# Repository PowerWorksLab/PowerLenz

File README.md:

# PowerLenz

PowerLenz - Power monitoring, management and analytics platform.

PowerLenz is a Sense-style energy monitor for Indian single-phase homes (230 V, 50 Hz). A clamp-on current sensor and a voltage sensor feed a 24-bit simultaneous-sampling ADC and an ESP32-S3, which finds appliance switching events and sends them to the cloud for classification. The hardware design is at paper stage: it is datasheet-checked, but nothing has been built or bench-tested yet.

## Documentation

Start with **[documentation/README.md](documentation/README.md)**. It gives the reading order, the design and its decisions, the bill of materials summary, safety notes and what is still open.

| Where | What it holds |
|---|---|
| [documentation/README.md](documentation/README.md) | The whole design in one page, with the reading order |
| [documentation/findings/](documentation/findings/) | Design reasoning, the datasheet verification checklist, datasheet links and the [bill of materials](documentation/findings/bill-of-materials.md) |
| [documentation/datasheets/](documentation/datasheets/README.md) | Local copies of the manufacturer datasheets, organised by function |
| [documentation/diagrams/](documentation/diagrams/) | Circuit diagrams and the calculation page |
| [documentation/presentations/](documentation/presentations/) | The slide deck and the scripts that build it |
| [documentation/brand/](documentation/brand/brand-guidelines.md) | Brand guidelines, [company purpose](documentation/brand/company-purpose.md), brand kit and sample screens |

## Safety

The mains side of the design is live 230 V. Nothing here is ready to be powered from the mains. Use an enclosure, correct clearance and creepage, and have the board reviewed by someone with mains-design experience first.

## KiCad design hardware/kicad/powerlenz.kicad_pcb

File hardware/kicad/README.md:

# KiCad design

The PowerLenz schematic, written as code and checked with KiCad's own electrical rules check (ERC).

| File | What it is |
|---|---|
| `powerlenz.kicad_pro` | KiCad project |
| `powerlenz.kicad_sch` | The schematic. **Generated**: edit `tools/build_schematic.py`, then re-run it. Hand edits in KiCad are overwritten. |
| `tools/build_schematic.py` | Describes the circuit, one function per block |
| `tools/kicad_gen.py`, `sexp.py`, `libinfo.py` | A small generator that takes symbols from KiCad's installed libraries |
| `sym-lib-table`, `fp-lib-table` | Library paths for the project |

## Rebuild and check

```
cd hardware/kicad
python3 tools/build_schematic.py
kicad-cli sch erc --format json --severity-all -o erc.json powerlenz.kicad_sch
kicad-cli sch export netlist --format kicadsexpr -o powerlenz.net powerlenz.kicad_sch
kicad-cli sch export pdf -o powerlenz.pdf powerlenz.kicad_sch
```

Needs KiCad 10 (`kicad-cli`) and Python 3. Connections are made with net labels and power symbols: every pin carrying the same net name is connected.

## PCB and 3D model

`tools/build_pcb.py` builds `powerlenz.kicad_pcb` from the schematic netlist: all parts are placed on a compact 154 x 86 mm board (with the ESP32-S3 DevKitC plugged into two 1x22 sockets; its outline and 22.86 mm row spacing are assumed) with a mains zone and a low-voltage zone, and every pad is assigned its net. `tools/route.py` then routes it with Freerouting in two separate runs (needs Java and the Freerouting jar in `~/tools`, not stored in the repo): the low-voltage side (0.25 mm signals, 0.5 mm power, 0.2 mm clearance, GND pour on the back copper) and the mains nets `L_IN`, `L_FUSED`, `N`, `ZA_P`, `ZP1`, `ZP2` (0.8 mm tracks, 3 mm clearance, the `Mains` net class in `powerlenz.kicad_pro`). Two 1 mm slots are milled along the isolation line at x = 56 mm (Edge.Cuts); `powerlenz.kicad_dru` relaxes the rule only for the terminal block J1, whose own pad gap is 2.48 mm.

**DRAFT: the mains clearance, the slot and the isolation spacing are my starting values (roughly IEC 60664-1 basic creepage for 250 V, pollution degree 2, plus margin) and have not been reviewed by anyone with mains-design experience.** Do not build this board. DRC reports no clearance, short or unconnected errors, only silkscreen and library-copy warnings.

```
python3 tools/build_pcb.py        # after the schematic is built
python3 tools/route.py            # needs ~/tools/freerouting*.jar; removes old tracks, then routes
kicad-cli pcb render --side top --rotate '-45,0,25' --width 2400 --height 1600 --quality high -o exports/3d/powerlenz-pcb-3d.png powerlenz.kicad_pcb
kicad-cli pcb export glb --subst-models -o exports/3d/powerlenz-pcb.glb powerlenz.kicad_pcb
python3 tools/make_step_models.py   # STEP stand-ins for the ZMPT107-1, DevKitC and fuse clip
kicad-cli pcb export step --subst-models --include-tracks --include-pads --include-zones --include-silkscreen --include-soldermask -o exports/3d/powerlenz-pcb.step powerlenz.kicad_pcb
```

| File | What it is |
|---|---|
| `exports/3d/powerlenz-pcb-3d.png`, `powerlenz-pcb-top.png` | Rendered pictures of the board |
| `exports/3d/powerlenz-pcb.glb` | The full 3D model (open in Blender, or any glTF viewer) |
| `exports/3d/powerlenz-pcb.step` | STEP for SolidWorks and other mechanical CAD, with copper, pads, silkscreen, solder mask and every part. The ZMPT107-1, the DevKitC and the fuse clip are simple coloured boxes from `tools/make_step_models.py` (assumed sizes, not manufacturer geometry); the other parts are KiCad library models. In SolidWorks use Open, Options, Import as assembly. |

Things to know about the 3D model:
- The ZMPT107-1 is a simple box (19 x 10 x 18.2 mm) with four pins, from the manufacturer's drawing, with its footprint taken from the same drawing and not yet checked against a real part.
- The varistor uses a 12 mm disc footprint as the nearest match for the 10 mm 10D561K.
- The BAT54 and BAV199 SOT-23 pad mappings are assumed (see the part notes).
- The mains and low-voltage zones are marked on the board. A real board also needs an isolation slot and proper creepage and clearance, reviewed by someone with mains-design experience.

## ERC notes

- `same_local_global_label` is set to ignore in `powerlenz.kicad_pro`. A few pins use a plain net label with the same name as a power net (for example +3V3A or GND) to keep stacked power symbols from overlapping. The nets are the same either way, and the exported netlist was compared before and after to confirm that.
- Footprints are not assigned yet, so the board stage is still ahead.

## Exports

`exports/powerlenz-schematic.pdf` and `exports/powerlenz-bom.csv` are generated with `kicad-cli` (see above). Re-export after any change.

## Status

The schematic is built block by block. Each block is committed once its ERC is clean. Footprints are not assigned yet. Nothing here has been built or tested; the open items in `documentation/README.md` still apply, and the mains side needs a design review before it is ever powered.

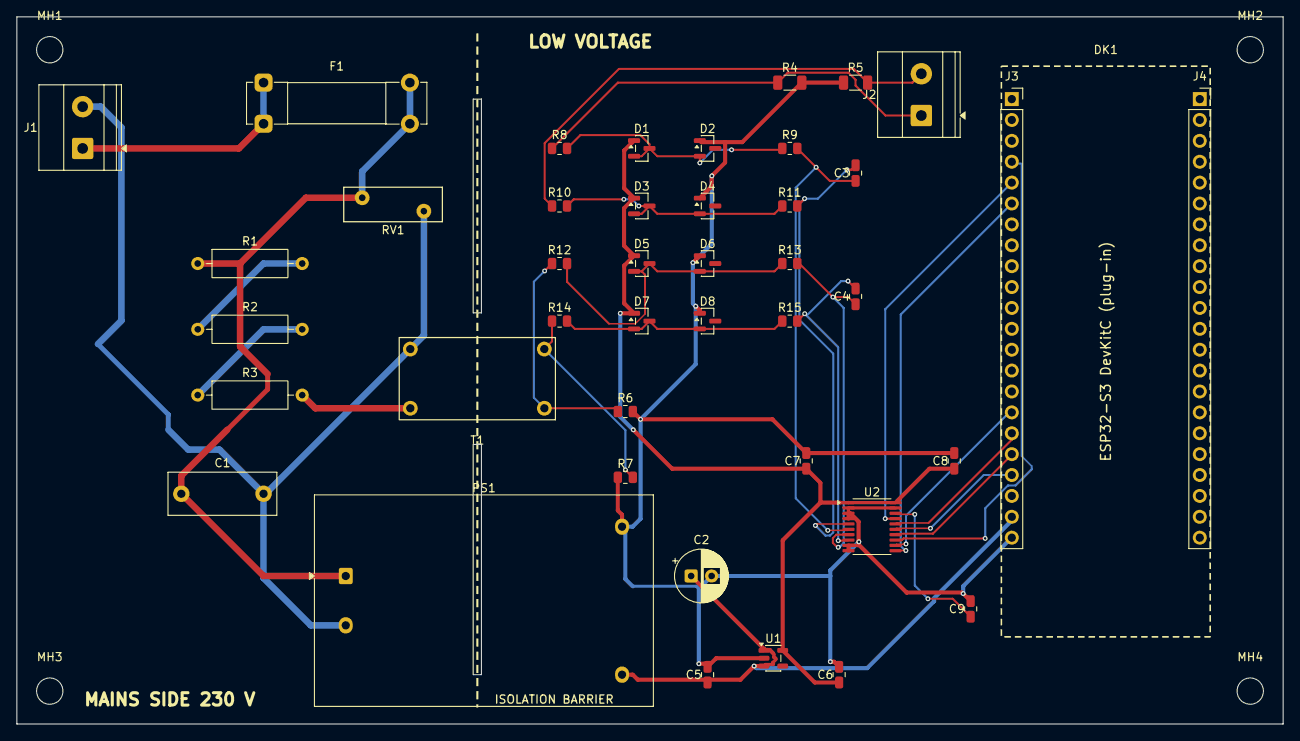
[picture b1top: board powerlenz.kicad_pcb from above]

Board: 2 copper layers, 154.0 x 86.0 mm, 47 parts (0 on the bottom side), 29 nets.

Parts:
C1: 0.1uF X2 275VAC; C_Rect_L13.0mm_W5.0mm_P10.00mm_FKS3_FKP3_MKS4
C2: 220uF 25V; CP_Radial_D6.3mm_P2.50mm
C3, C4: 10nF C0G; C_0805_2012Metric
C5, C6, C7, C8: 1uF 50V X7R; C_0805_2012Metric
C9: 220nF 50V X7R; C_0805_2012Metric
D1, D3, D5, D7: BAT54; SOT-23
D2, D4, D6, D8: BAV199; SOT-23
DK1: ESP32-S3-DevKitC-1
F1: 1A T 250V; Fuseholder_Clip-5x20mm_Bel_FC-203-22_Lateral_P17.80x5.00mm_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
J1: Mains in; TerminalBlock_Phoenix_MKDS-1,5-2-5.08_1x02_P5.08mm_Horizont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
J2: CT SCT-013-000; TerminalBlock_Phoenix_MKDS-1,5-2-5.08_1x02_P5.08mm_Horizont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
J3: DevKitC row A (J1 pins); PinSocket_1x22_P2.54mm_Vertical
J4: DevKitC row B (J3 pins); PinSocket_1x22_P2.54mm_Vertical
MH1, MH2, MH3, MH4: MountingHole_3.2mm_M3
PS1: HLK-5M05; Converter_ACDC_Hi-Link_HLK-5Mxx
R1, R2, R3: 39k 1% 1/2W; R_Axial_DIN0309_L9.0mm_D3.2mm_P12.70mm_Horizontal
R4, R5: 6.49R 1%; R_1206_3216Metric
R6, R7: 24.9R 1%; R_0805_2012Metric
R8, R10, R12, R14: 1k 1%; R_0805_2012Metric
R9, R11, R13, R15: 100R 1%; R_0805_2012Metric
RV1: 10D561K; RV_Disc_D12mm_W4.2mm_P7.5mm
T1: ZMPT107-1
U1: LP5907-3.3; SOT-23-5
U2: ADS131M04; TSSOP-20_4.4x6.5mm_P0.65mm

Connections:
+3V3A: C6.1, C7.1, C8.1, D1.1, D3.1, D5.1, D7.1, U1.5, U2.1, U2.20
+5V: C2.1, C5.1, J3.21, PS1.4, U1.1, U1.3
ADC_CAP: C9.1, U2.18
ADC_CLKIN: J3.5, U2.17
ADC_CS: J3.16, U2.12
ADC_DIN: J3.17, U2.16
ADC_DOUT: J3.19, U2.15
ADC_DRDY: J3.4, U2.13
ADC_RESET: J3.6, U2.11
ADC_SCLK: J3.18, U2.14
CH1N: C3.2, R11.2, U2.5
CH1P: C3.1, R9.2, U2.6
CH2N: C4.2, R15.2, U2.8
CH2P: C4.1, R13.2, U2.7
CT_N: J2.2, R5.2, R10.1
CT_N_C: D3.2, D3.3, D4.2, R10.2, R11.1
CT_P: J2.1, R4.1, R8.1
CT_P_C: D1.2, D1.3, D2.2, R8.2, R9.1
GND: C2.2, C5.2, C6.2, C7.2, C8.2, C9.2, D2.1, D4.1, D6.1, D8.1, J3.22, PS1.3, R4.2, R5.1, R6.2, R7.1, U1.2, U2.2, U2.3, U2.4, U2.9, U2.10, U2.19
L_FUSED: C1.1, F1.2, PS1.1, R1.1, RV1.1
L_IN: F1.1, J1.1
N: C1.2, J1.2, PS1.2, RV1.2, T1.1
V_N: R7.2, R14.1, T1.3
V_N_C: D7.2, D7.3, D8.2, R14.2, R15.1
V_P: R6.1, R12.1, T1.4
V_P_C: D5.2, D5.3, D6.2, R12.2, R13.1
ZA_P: R3.2, T1.2
ZP1: R1.2, R2.1
ZP2: R2.2, R3.1

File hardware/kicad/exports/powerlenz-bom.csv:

"Reference","Value","Qty","Footprint","MPN","Manufacturer"
"C1","0.1uF X2 275VAC","1","Capacitor_THT:C_Rect_L13.0mm_W5.0mm_P10.00mm_FKS3_FKP3_MKS4","",""
"C2","220uF 25V","1","Capacitor_THT:CP_Radial_D6.3mm_P2.50mm","",""
"C3,C4","10nF C0G","2","Capacitor_SMD:C_0805_2012Metric","0805N103J500CT","Walsin"
"C5,C6,C7,C8","1uF 50V X7R","4","Capacitor_SMD:C_0805_2012Metric","CC0805KKX7R9BB105","Yageo"
"C9","220nF 50V X7R","1","Capacitor_SMD:C_0805_2012Metric","0805B224K500CT","Walsin"
"D1,D3,D5,D7","BAT54","4","Package_TO_SOT_SMD:SOT-23","BAT54-7-F","Diodes Inc"
"D2,D4,D6,D8","BAV199","4","Package_TO_SOT_SMD:SOT-23","BAV199-7-F","Diodes Inc"
"F1","1A T 250V","1","Fuse:Fuseholder_Clip-5x20mm_Bel_FC-203-22_Lateral_P17.80x5.00mm_D1.17mm_Horizontal","5HT 1-R","Bel Fuse"
"J1","Mains in","1","TerminalBlock_Phoenix:TerminalBlock_Phoenix_MKDS-1,5-2-5.08_1x02_P5.08mm_Horizontal","",""
"J2","CT SCT-013-000","1","TerminalBlock_Phoenix:TerminalBlock_Phoenix_MKDS-1,5-2-5.08_1x02_P5.08mm_Horizontal","",""
"J3","To DevKitC","1","Connector_PinHeader_2.54mm:PinHeader_1x09_P2.54mm_Vertical","",""
"PS1","HLK-5M05","1","Converter_ACDC:Converter_ACDC_Hi-Link_HLK-5Mxx","","Hi-Link"
"R1,R2,R3","39k 1% 1/2W","3","Resistor_THT:R_Axial_DIN0309_L9.0mm_D3.2mm_P12.70mm_Horizontal","MF50 39K",""
"R4,R5","6.49R 1%","2","Resistor_SMD:R_1206_3216Metric","CRCW12066R49FKEA","Vishay"
"R6,R7","24.9R 1%","2","Resistor_SMD:R_0805_2012Metric","RC0805FR-0724R9L","Yageo"
"R8,R10,R12,R14","1k 1%","4","Resistor_SMD:R_0805_2012Metric","RC0805FR-071KL","Yageo"
"R9,R11,R13,R15","100R 1%","4","Resistor_SMD:R_0805_2012Metric","RC0805FR-07100RL","Yageo"
"RV1","10D561K","1","Varistor:RV_Disc_D12mm_W4.2mm_P7.5mm","MOV-10D561K","Bourns"
"T1","ZMPT107-1","1","powerlenz:ZMPT107-1","","Zeming"
"U1","LP5907-3.3","1","Package_TO_SOT_SMD:SOT-23-5","LP5907MFX-3.3/NOPB","Texas Instruments"
"U2","ADS131M04","1","Package_SO:TSSOP-20_4.4x6.5mm_P0.65mm","ADS131M04IPWR","Texas Instruments"

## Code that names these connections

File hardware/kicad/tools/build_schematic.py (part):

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    y = 60.96
    s.part("Connector", "Screw_Terminal_01x02", "Mains in", (33.02, y), {1: "L_IN", 2: "N"}, prefix="J",
           extra={"Note": "Pin 1 = live, pin 2 = neutral"})
    s.part("Device", "Fuse", "1A T 250V", (68.58, y), {1: "L_IN", 2: "L_FUSED"}, prefix="F", rot=90,
           extra={"MPN": "5HT 1-R", "Manufacturer": "Bel Fuse",
                  "Note": "Ceramic time-lag, listed 1.5 kA at 250 VAC; Bel datasheet not yet read"})
    s.part("Device", "Varistor", "10D561K", (101.6, y), {1: "L_FUSED", 2: "N"}, prefix="RV", rot=90,
           extra={"MPN": "MOV-10D561K", "Manufacturer": "Bourns", "Note": "350 VAC / 460 VDC, 2.5 kA, 70 J"})
    # ZMPT107-1 primary string: 3 x 39 k in series = 117 k (about 2 mA at 230 V)
    s.part("Device", "R", "39k 1% 1/2W", (132.08, y), {1: "L_FUSED", 2: "ZP1"}, prefix="R", rot=90,
           extra={"MPN": "MF50 39K", "Note": "Series string R1-R3 sets about 2 mA through the ZMPT107-1 primary"})
    s.part("Device", "R", "39k 1% 1/2W", (157.48, y), {1: "ZP1", 2: "ZP2"}, prefix="R", rot=90,
           extra={"MPN": "MF50 39K"})
    s.part("Device", "R", "39k 1% 1/2W", (182.88, y), {1: "ZP2", 2: "ZA_P"}, prefix="R", rot=90,
           extra={"MPN": "MF50 39K"})
    s.part("Device", "Transformer_1P_1S", "ZMPT107-1", (228.6, y), {1: "ZA_P", 2: "N", 4: "V_P", 3: "V_N"}, prefix="T",
           extra={"Manufacturer": "Zeming", "Note": "2 mA : 2 mA, 3000 V isolated. Windings are interchangeable (1000:1000); "
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    s.text("CT current sensor: burden 2 x 6.49 ohm, midpoint to GND", 15.24, 152.4, 1.27)
    s.part("Connector", "Screw_Terminal_01x02", "CT SCT-013-000", (25.4, yi), {1: "CT_P", 2: "CT_N"}, prefix="J",
           extra={"Note": "Current-output CT (100 A : 50 mA). Never leave the CT secondary open"})
    s.part("Device", "R", "6.49R 1%", (68.58, yi), {1: "CT_P", 2: "GND"}, prefix="R", rot=90,
           extra={"MPN": "CRCW12066R49FKEA", "Manufacturer": "Vishay", "Note": "Burden half; 2 x 6.49 = 12.98 ohm"})
    s.part("Device", "R", "6.49R 1%", (96.52, yi), {1: "GND", 2: "CT_N"}, prefix="R", rot=90,
           extra={"MPN": "CRCW12066R49FKEA", "Manufacturer": "Vishay"})
    s.text("ZMPT107-1 sampling: 2 x 24.9 ohm = about 50 ohm, midpoint to GND", 134.62, 152.4, 1.27)
    s.part("Device", "R", "24.9R 1%", (160.02, yi), {1: "V_P", 2: "GND"}, prefix="R", rot=90,
           extra={"MPN": "RC0805FR-0724R9L", "Manufacturer": "Yageo", "Note": "Sampling resistor half"})
    s.part("Device", "R", "24.9R 1%", (187.96, yi), {1: "GND", 2: "V_N"}, prefix="R", rot=90,
           extra={"MPN": "RC0805FR-0724R9L", "Manufacturer": "Yageo"})

    legs = [  # (row y, input net, clamp node, mid net, ADC net, label)
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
